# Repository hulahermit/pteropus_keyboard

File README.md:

pteropus keyboard
=================

Another Miryoku inspired 36-key keyboard.

After seeing the Miryoku layout on the web, I really wanted to try with a 36-key keyboard.

I looked some keyboards, like Iris, Crowboard, Kyria, etc., and I feel that I need to create keyboard geometry that fits my hands.

So I printed those layout and modify them to fit my hands and hopefully it will work.

Features
--------
This keyboard is a non-split linear staggered keyboard, like Crowboard or absolem.

Using a non-split keyboard, I can just use one microcontroller, and it simplify the design.

STM32F072 microcontroller
---------
This microcontroller is a crystal-less USB 2.0 controller, and it is embeded with serial resistors for USB_DP/USB_DM 

and a pull-up resistor for USB_DP, so it reduced the part count and simplify the trace routing.

Sourcing the keyboard
---------------------
This keyboard uses SMD components, except the type-c connector, so it came almost finished from the factory with PCB assembly service.

I use JLCPCB, so the part number shall be changed if use otherwise.

- BOM: pteropus BOM.csv
- Component position: pteropus-bottom-pos.csv

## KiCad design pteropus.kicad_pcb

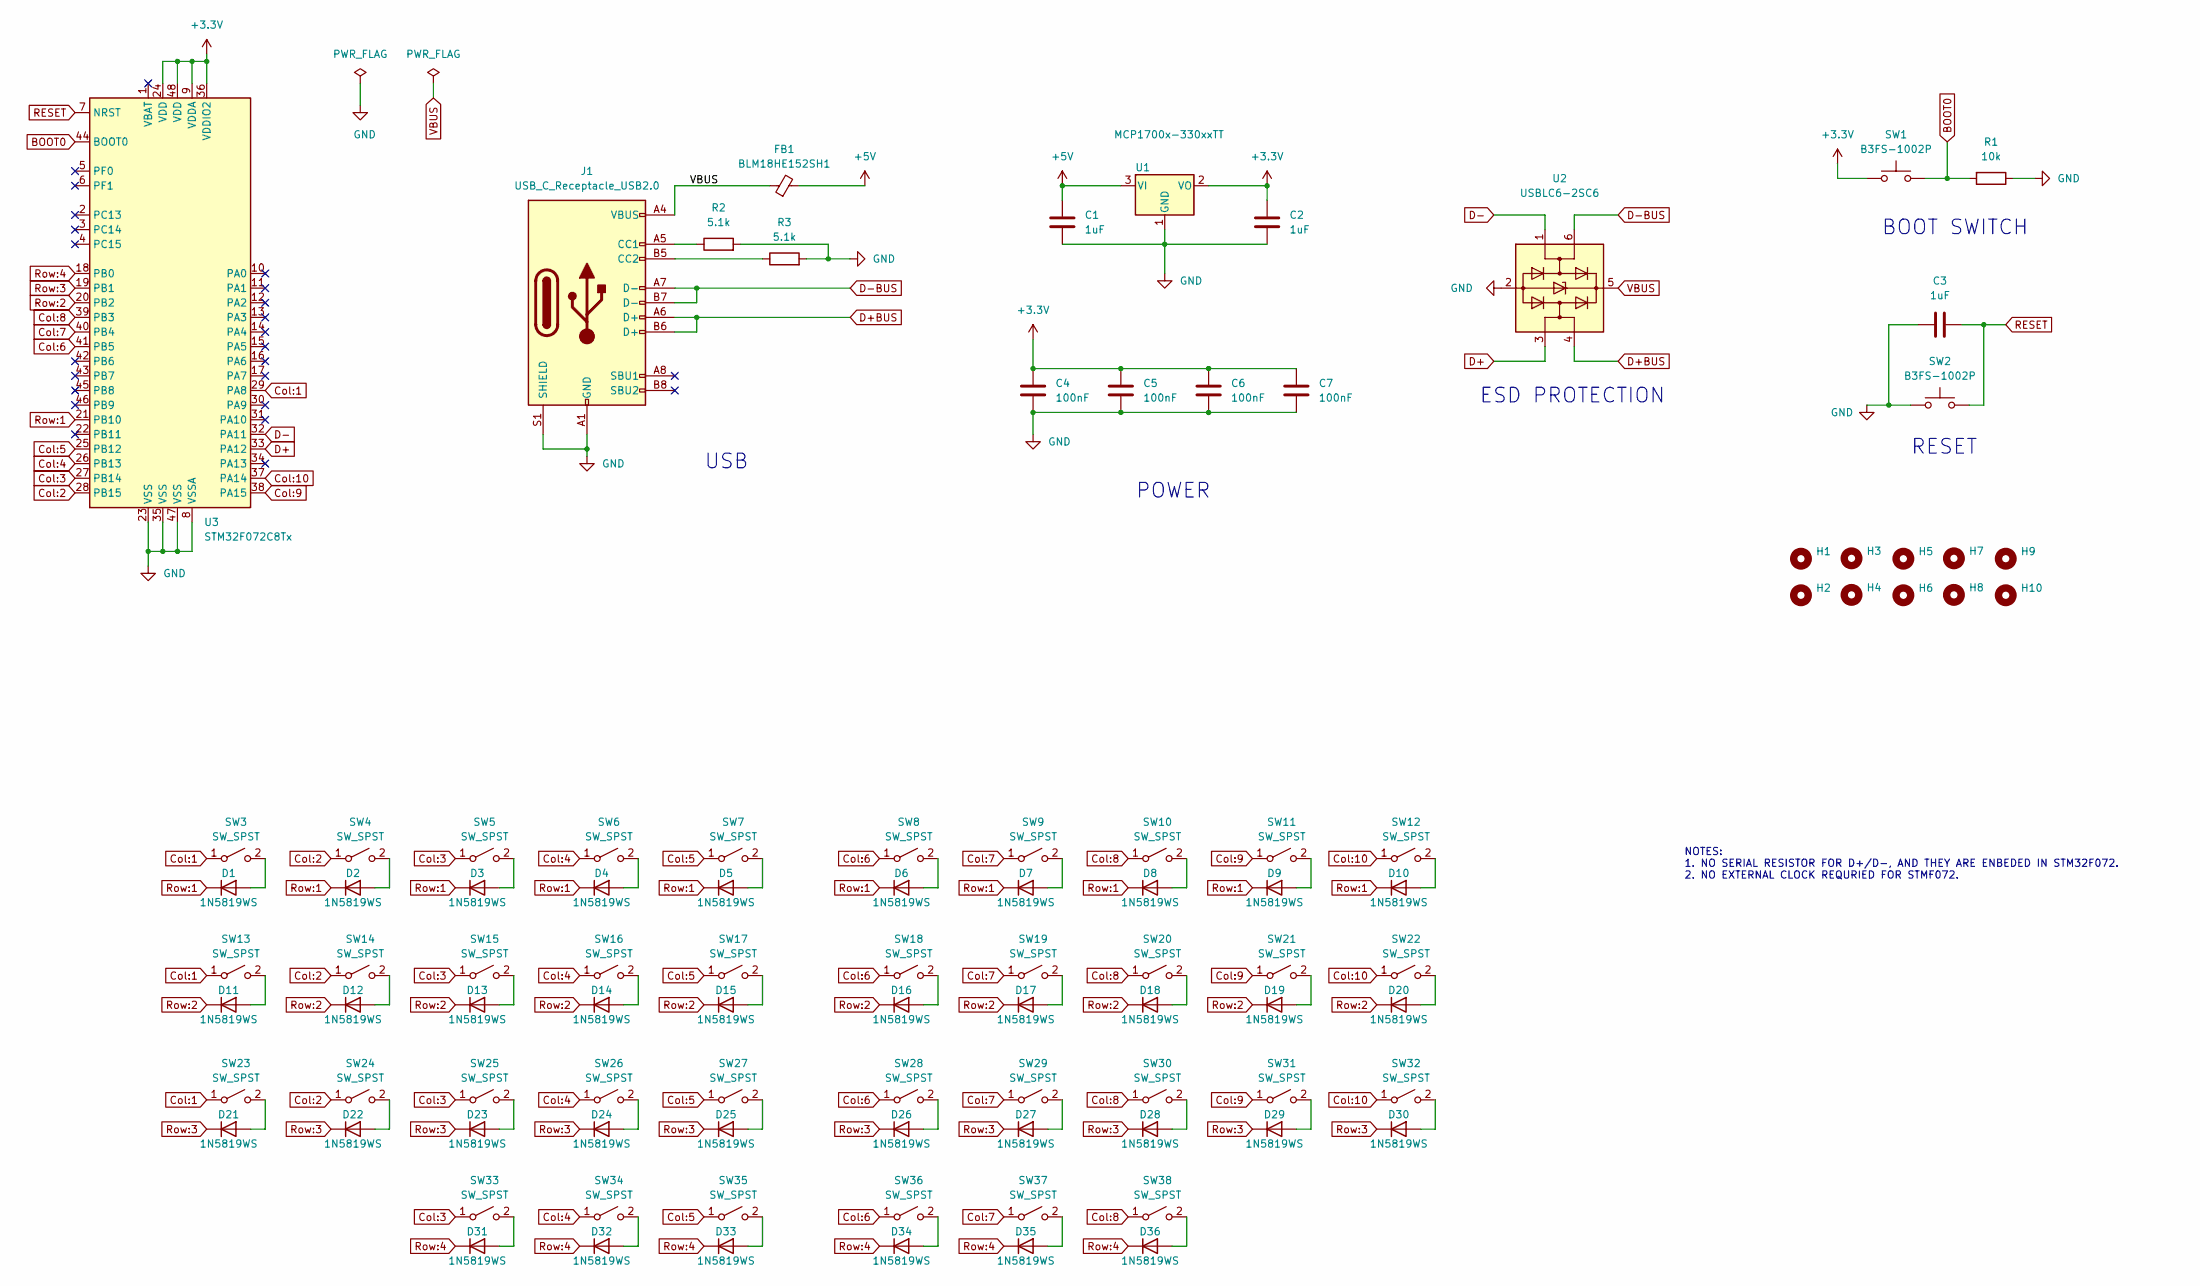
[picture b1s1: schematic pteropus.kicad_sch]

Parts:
C1, C2, C3: 1uF; C_0805_2012Metric; LCSC Part Number C28323
C4, C5, C6, C7: 100nF; C_0603_1608Metric; LCSC Part Number C14663
D1, D2, D3, D4, D5, D6, D7, D8, D9, D10, D11, D12, D13, D14, D15, D16, D17, D18, D19, D20, D21, D22, D23, D24, D25, D26, D27, D28, D29, D30, D31, D32, D33, D34, D35, D36: 1N5819WS; D_SOD-323; LCSC Part Number C191023
FB1: BLM18HE152SH1; R_0603_1608Metric; LCSC Part Number C596494
H1, H2, H3, H4, H5, H6, H7, H8, H9, H10: M3; MountingHole_3.2mm_M3_DIN965; LCSC Part Number n/a
J1: USB_C_Receptacle_USB2.0; USB_C_Receptacle_GCT_USB4085; LCSC Part Number n/a
R1: 10k; R_0805_2012Metric; LCSC Part Number C17414
R2, R3: 5.1k; R_0805_2012Metric; LCSC Part Number C27834
SW1, SW2: B3FS-1002P; SW_SPST_Omron_B3FS-100xP; LCSC Part Number C87038
SW3, SW4, SW5, SW6, SW7, SW8, SW9, SW10, SW11, SW12, SW13, SW14, SW15, SW16, SW17, SW18, SW19, SW20, SW21, SW22, SW23, SW24, SW25, SW26, SW27, SW28, SW29, SW30, SW31, SW32, SW33, SW34, SW35, SW36, SW37, SW38: SW_SPST; Kailh_socket_MX; LCSC Part Number n/a
U1: MCP1700x-330xxTT; SOT-23; LCSC Part Number C39051
U2: USBLC6-2SC6; SOT-23-6; LCSC Part Number C7519
U3: STM32F072C8Tx; LQFP-48_7x7mm_P0.5mm; LCSC Part Number C80488

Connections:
+3.3V: C2.1, C4.1, C5.1, C6.1, C7.1, SW1.1, U1.2 (VO), U3.9 (VDDA), U3.24 (VDD), U3.36 (VDDIO2), U3.48 (VDD)
+5V: C1.1, FB1.2, U1.3 (VI)
BOOT0: R1.2, SW1.2, U3.44 (BOOT0)
Col:1: SW3.1 (A), SW13.1 (A), SW23.1 (A), U3.29 (PA8)
Col:2: SW4.1 (A), SW14.1 (A), SW24.1 (A), U3.28 (PB15)
Col:3: SW5.1 (A), SW15.1 (A), SW25.1 (A), SW33.1 (A), U3.27 (PB14)
Col:4: SW6.1 (A), SW16.1 (A), SW26.1 (A), SW34.1 (A), U3.26 (PB13)
Col:5: SW7.1 (A), SW17.1 (A), SW27.1 (A), SW35.1 (A), U3.25 (PB12)
Col:6: SW8.1 (A), SW18.1 (A), SW28.1 (A), SW36.1 (A), U3.41 (PB5)
Col:7: SW9.1 (A), SW19.1 (A), SW29.1 (A), SW37.1 (A), U3.40 (PB4)
Col:8: SW10.1 (A), SW20.1 (A), SW30.1 (A), SW38.1 (A), U3.39 (PB3)
Col:9: SW11.1 (A), SW21.1 (A), SW31.1 (A), U3.38 (PA15)
Col:10: SW12.1 (A), SW22.1 (A), SW32.1 (A), U3.37 (PA14)
D+: U2.3 (I/O2), U3.33 (PA12)
D+BUS: J1.A6 (D+), J1.B6 (D+), U2.4 (I/O2)
D-: U2.1 (I/O1), U3.32 (PA11)
D-BUS: J1.A7 (D-), J1.B7 (D-), U2.6 (I/O1)
GND: C1.2, C2.2, C3.1, C4.2, C5.2, C6.2, C7.2, J1.A1 (GND), J1.A12 (GND), J1.B1 (GND), J1.B12 (GND), J1.S1 (SHIELD), R1.1, R2.2, R3.2, SW2.1, U1.1 (GND), U2.2 (GND), U3.8 (VSSA), U3.23 (VSS), U3.35 (VSS), U3.47 (VSS)
unnamed: D1.2 (A), SW3.2 (B)
unnamed: D2.2 (A), SW4.2 (B)
unnamed: D3.2 (A), SW5.2 (B)
unnamed: D4.2 (A), SW6.2 (B)
unnamed: D5.2 (A), SW7.2 (B)
unnamed: D6.2 (A), SW8.2 (B)
unnamed: D7.2 (A), SW9.2 (B)
unnamed: D8.2 (A), SW10.2 (B)
unnamed: D9.2 (A), SW11.2 (B)
unnamed: D10.2 (A), SW12.2 (B)
unnamed: D11.2 (A), SW13.2 (B)
unnamed: D12.2 (A), SW14.2 (B)
unnamed: D13.2 (A), SW15.2 (B)
unnamed: D14.2 (A), SW16.2 (B)
unnamed: D15.2 (A), SW17.2 (B)
unnamed: D16.2 (A), SW18.2 (B)
unnamed: D17.2 (A), SW19.2 (B)
unnamed: D18.2 (A), SW20.2 (B)
unnamed: D19.2 (A), SW21.2 (B)
unnamed: D20.2 (A), SW22.2 (B)
unnamed: D21.2 (A), SW23.2 (B)
unnamed: D22.2 (A), SW24.2 (B)
unnamed: D23.2 (A), SW25.2 (B)
unnamed: D24.2 (A), SW26.2 (B)
unnamed: D25.2 (A), SW27.2 (B)
unnamed: D26.2 (A), SW28.2 (B)
unnamed: D27.2 (A), SW29.2 (B)
unnamed: D28.2 (A), SW30.2 (B)
unnamed: D29.2 (A), SW31.2 (B)
unnamed: D30.2 (A), SW32.2 (B)
unnamed: D31.2 (A), SW33.2 (B)
unnamed: D32.2 (A), SW34.2 (B)
unnamed: D33.2 (A), SW35.2 (B)
unnamed: D34.2 (A), SW36.2 (B)
unnamed: D35.2 (A), SW37.2 (B)
unnamed: D36.2 (A), SW38.2 (B)
unnamed: J1.A5 (CC1), R2.1
unnamed: J1.B5 (CC2), R3.1
RESET: C3.2, SW2.2, U3.7 (NRST)
Row:1: D1.1 (K), D2.1 (K), D3.1 (K), D4.1 (K), D5.1 (K), D6.1 (K), D7.1 (K), D8.1 (K), D9.1 (K), D10.1 (K), U3.21 (PB10)
Row:2: D11.1 (K), D12.1 (K), D13.1 (K), D14.1 (K), D15.1 (K), D16.1 (K), D17.1 (K), D18.1 (K), D19.1 (K), D20.1 (K), U3.20 (PB2)
Row:3: D21.1 (K), D22.1 (K), D23.1 (K), D24.1 (K), D25.1 (K), D26.1 (K), D27.1 (K), D28.1 (K), D29.1 (K), D30.1 (K), U3.19 (PB1)
Row:4: D31.1 (K), D32.1 (K), D33.1 (K), D34.1 (K), D35.1 (K), D36.1 (K), U3.18 (PB0)
VBUS: FB1.1, J1.A4 (VBUS), J1.A9 (VBUS), J1.B4 (VBUS), J1.B9 (VBUS), U2.5 (VBUS)

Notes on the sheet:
POWER
ESD PROTECTION
BOOT SWITCH
USB
NOTES: 1. NO SERIAL RESISTOR FOR D+/D-, AND THEY ARE ENBEDED IN STM32F072. 2. NO EXTERNAL CLOCK REQURIED FOR STMF072.
RESET

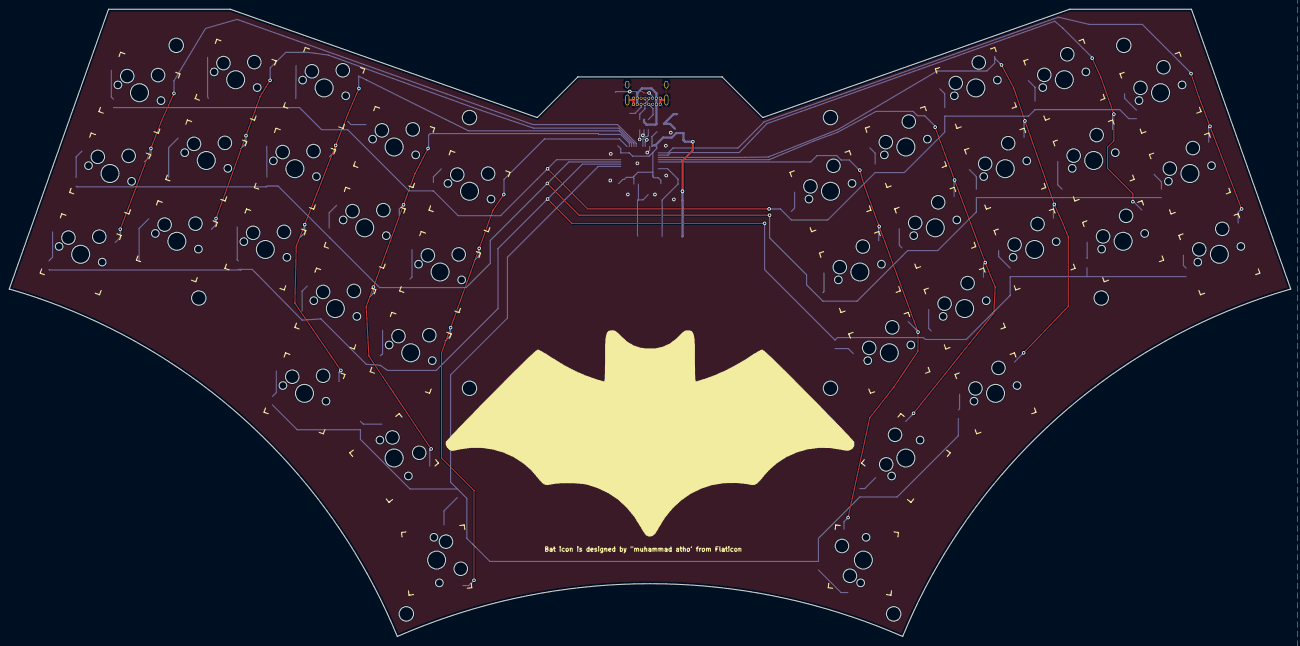
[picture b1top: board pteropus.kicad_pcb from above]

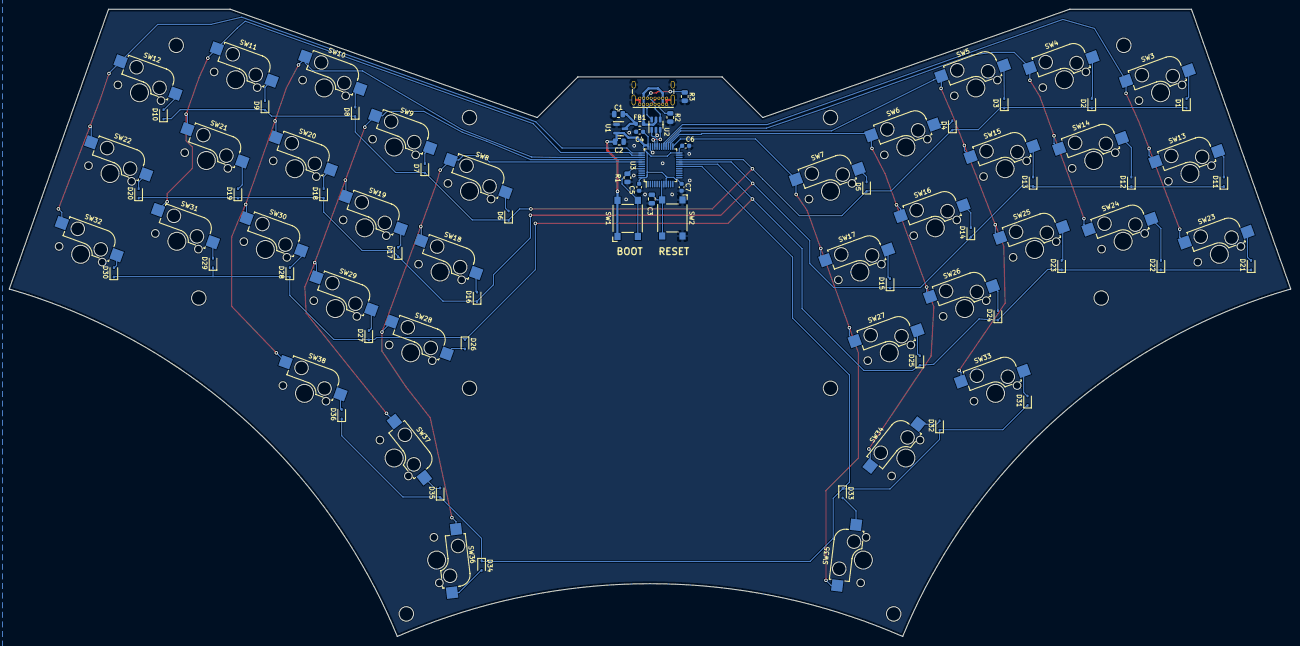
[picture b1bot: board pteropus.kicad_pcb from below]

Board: 2 copper layers, 284.0 x 139.0 mm, 99 parts (53 on the bottom side), 62 nets.

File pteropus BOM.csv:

Designator,Components,Footprint,LCSC Part Number,Qty
"C1,C2,C3",1uF,Capacitor_SMD:C_0805_2012Metric,C28323,3
"C4,C5,C6,C7",100nF,Capacitor_SMD:C_0603_1608Metric,C14663,4
"D1,D2,D3,D4,D5,D6,D7,D8,D9,D10,D11,D12,D13,D14,D15,D16,D17,D18,D19,D20,D21,D22,D23,D24,D25,D26,D27,D28,D29,D30,D31,D32,D33,D34,D35,D36",1N5819WS,Diode_SMD:D_SOD-323,C191023,36
FB1,BLM18HE152SH1,Resistor_SMD:R_0603_1608Metric,C596494,1
R1,10k,Resistor_SMD:R_0805_2012Metric,C17414,1
"R2, R3",5.1k,Resistor_SMD:R_0805_2012Metric,C27834,2
"SW1, SW2",B3FS-1002P,Button_Switch_SMD:SW_SPST_Omron_B3FS-100xP,C87038,2
U1,MCP1700x-330xxTT,Package_TO_SOT_SMD:SOT-23,C39051,1
U2,USBLC6-2SC6,Package_TO_SOT_SMD:SOT-23-6,C7519,1
U3,STM32F072C8Tx,Package_QFP:LQFP-48_7x7mm_P0.5mm,C80488,1

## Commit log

2023-03-15 Add images and update BOM
2023-03-15 Update BOM.
2023-03-24 Relocate D29 diode.
